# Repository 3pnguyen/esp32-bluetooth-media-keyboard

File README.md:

# esp32-bluetooth-media-keyboard 

## Electronic project that provides the same control as wireless earbuds.

<div align="center">
  
</div>

## ✨ About

This is a repostiory for an electroincs project designed to fit in an Altoids tin with wireless capability to control music playback via Bluetooth. Featuring a 400mAh battery, the circuit also includes a voltage divider + voltage follower setup to reliably measure the battery level & a micro limit switch to trigger sleeping when not in use. The user interface is equiped with 4 push buttons + a compact RGB LED.

When I created the initial prototype (and didn't finish the project), I was not as developed in my electronics skill. Due to being picked up for [Lionstride's Inventeam](https://github.com/3pnguyen/lionstride-inventeam-2026), the project would go under a 6 month hiatus. Drawing closer to the end of the school year, I realized that I could revive the project better than ever. By 6 months, I leveled up my schematic design game, learned to design PCBs, and use programming tools such as PlatformIO. I decided to redesign nearly the entire thing:

<div align="center">
    <table>
        <tr>
            <td> <p> Before: </p> </td>
            <td> <p> After: </p> </td>
        </tr>
        <tr>
            <td>  </td>
            <td>  </td>
        </tr>
    </table>
</div>

V2 was a big leap from the initial prototype. But it never ended up being created because it was too expensive. So I went with a hybrid version, V3:

<div align="center">
  
</div>

V3 took the pros out of the prototype and V2 - it made the perfect balance of cost and complexity.

It was perfect that the project dragged out the way it did, because I ended up making it better than ever. Other than that, this project has become the benchmark for all of the progress I made in my first year of high school. Other than the project's repository, this is a time capsule for how far I've come - and I'll never forget that.

## 📐 CAD

[Amazing CAD here](https://cad.onshape.com/documents/83f792e68010cb24d3ada2b4/w/ca8c8df538ed234a2d133709/e/c846efb1a51148007d1a6c65?renderMode=0&uiState=69af7c17ebe184b914fd710f)

<div align="center">
    <table>
        <tr>
            <td> <p> Prototype: </p> </td>
            <td> <p> V3: </p> </td>
        </tr>
        <tr>
            <td>  </td>
            <td>  </td>
        </tr>
    </table>
</div>

I was too lazy to finish the CAD for V3   <3

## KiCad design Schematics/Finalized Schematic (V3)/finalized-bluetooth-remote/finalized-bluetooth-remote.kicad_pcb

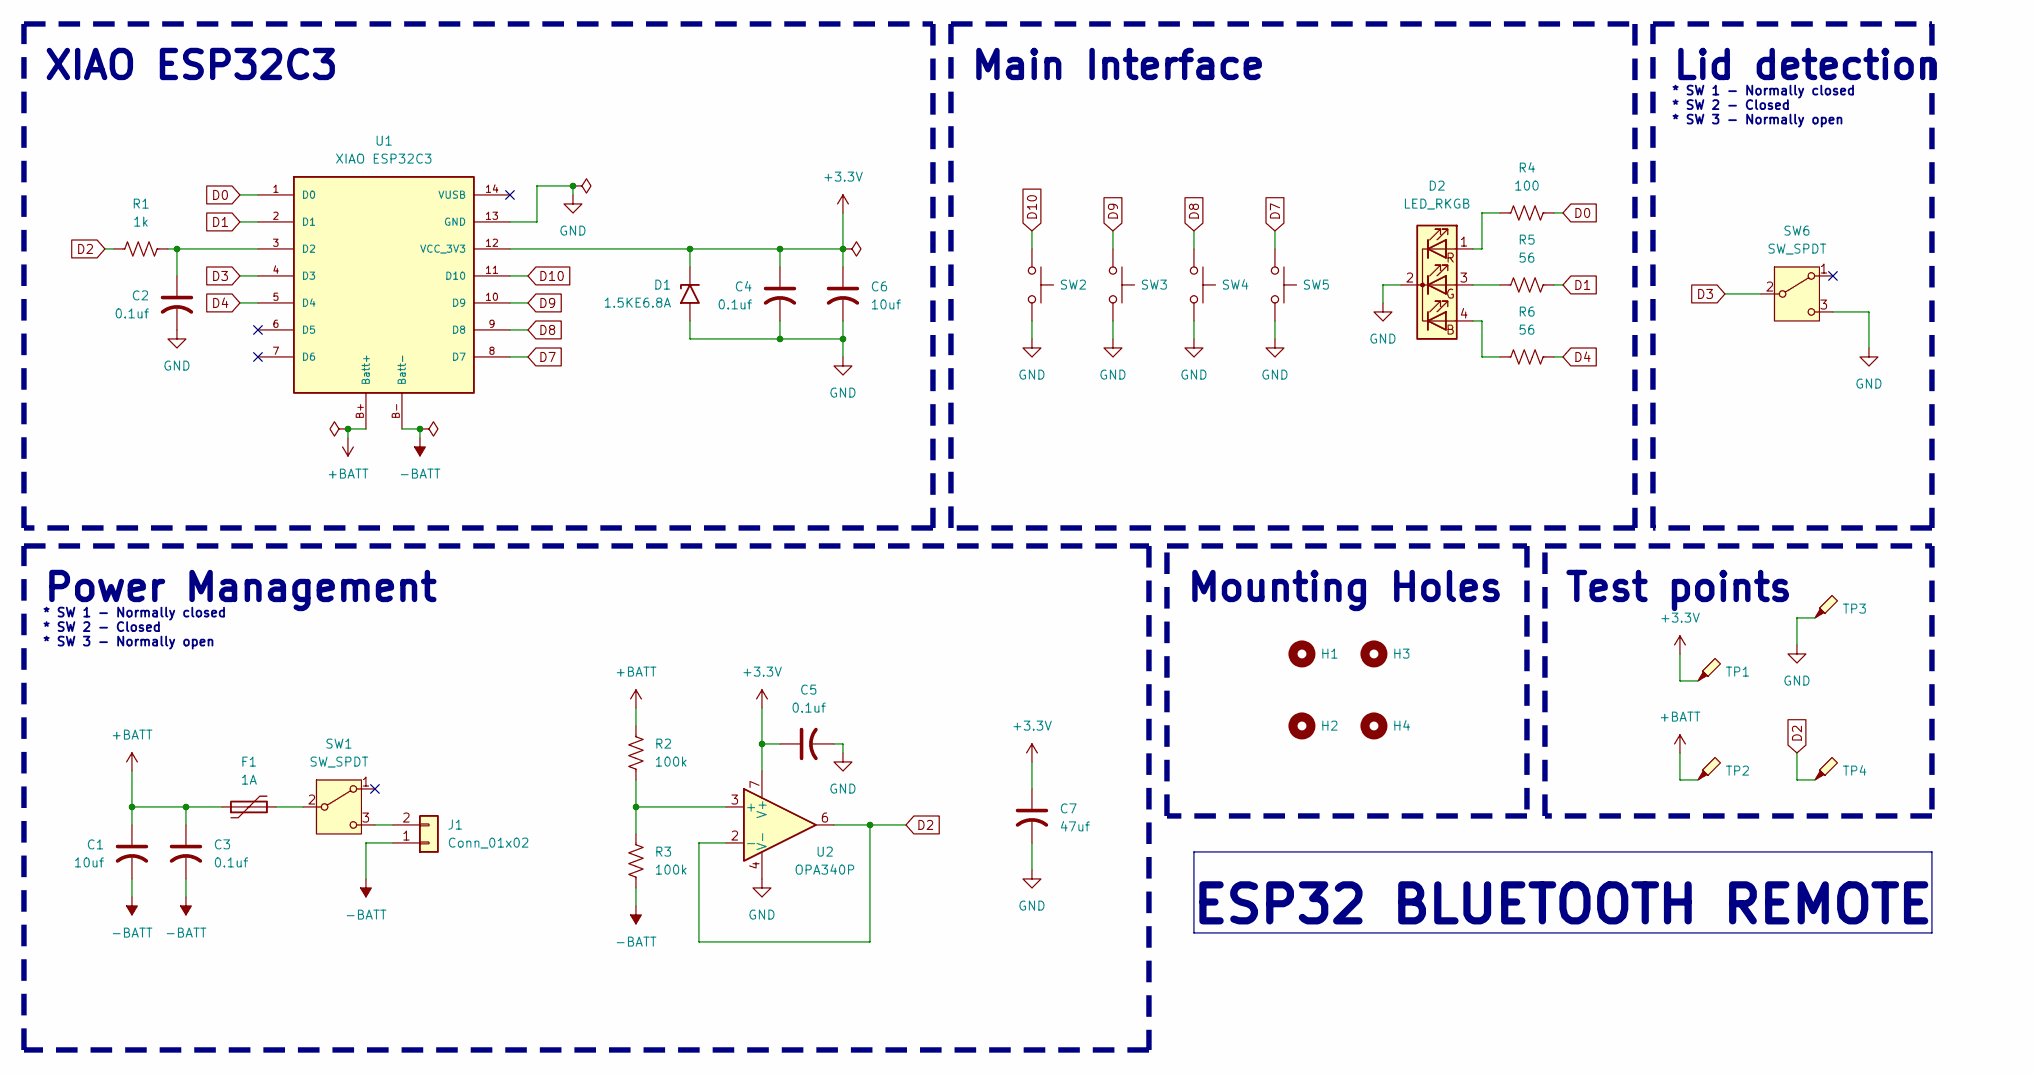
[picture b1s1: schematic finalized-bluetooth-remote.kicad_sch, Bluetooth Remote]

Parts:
C1, C6: 10uf; C_Disc_D5.1mm_W3.2mm_P5.00mm
C2, C3, C4, C5: 0.1uf; C_Disc_D5.1mm_W3.2mm_P5.00mm
C7: 47uf; CP_Radial_D5.0mm_P2.00mm
D1: 1.5KE6.8A; D_DO-201AE_P15.24mm_Horizontal
D2: LED_RKGB; LED_D5.0mm-4_RGB
F1: 1A; Fuse_Bourns_MF-RG300
H1, H2, H3, H4: MountingHole; MountingHole_2.2mm_M2
J1: Conn_01x02; JST_PH_S2B-PH-SM4-TB_1x02-1MP_P2.00mm_Horizontal
R1: 1k; R_Axial_DIN0207_L6.3mm_D2.5mm_P7.62mm_Horizontal
R2, R3: 100k; R_Axial_DIN0207_L6.3mm_D2.5mm_P7.62mm_Horizontal
R4: 100; R_Axial_DIN0207_L6.3mm_D2.5mm_P7.62mm_Horizontal
R5, R6: 56; R_Axial_DIN0207_L6.3mm_D2.5mm_P7.62mm_Horizontal
SW1, SW6: SW_SPDT; PinHeader_1x03_P2.54mm_Vertical
SW2, SW3, SW4, SW5: SW_Push; SW_PUSH_6mm_H7.3mm
TP1, TP2, TP3, TP4: TestPoint_Probe; TestPoint_Pad_D2.0mm
U1: XIAO ESP32C3; Xiao_esp32c3
U2: OPA340P; DIP-8_W7.62mm

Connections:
+3.3V: C4.1, C5.1, C6.1, C7.1, D1.1 (A1), TP1.1, U1.12 (VCC_3V3), U2.7 (V+)
+BATT: C1.1, C3.1, F1.1, R2.1, TP2.1, U1.B+ (Batt+)
-BATT: C1.2, C3.2, J1.1, R3.2, U1.B- (Batt-)
D0: R4.2, U1.1 (D0)
D1: R5.2, U1.2 (D1)
D2: R1.1, TP4.1, U2.2 (-), U2.6
D3: SW6.2 (B), U1.4 (D3)
D4: R6.2, U1.5 (D4)
D7: SW5.1, U1.8 (D7)
D8: SW4.1, U1.9 (D8)
D9: SW3.1, U1.10 (D9)
D10: SW2.1, U1.11 (D10)
GND: C2.2, C4.2, C5.2, C6.2, C7.2, D1.2 (A2), D2.2 (K), SW2.2, SW3.2, SW4.2, SW5.2, SW6.3 (C), TP3.1, U1.13 (GND), U2.4 (V-)
unnamed: D2.4 (BA), R6.1
unnamed: D2.3 (GA), R5.1
unnamed: D2.1 (RA), R4.1
unnamed: J1.2, SW1.3 (C)
unnamed: F1.2, SW1.2 (B)
unnamed: C2.1, R1.2, U1.3 (D2)
unnamed: R2.2, R3.1, U2.3 (+)

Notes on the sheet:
* SW 1 - Normally closed * SW 2 - Closed * SW 3 - Normally open
Mounting Holes
ESP32 BLUETOOTH REMOTE
Lid detection
Main Interface
Power Management
Test points
XIAO ESP32C3

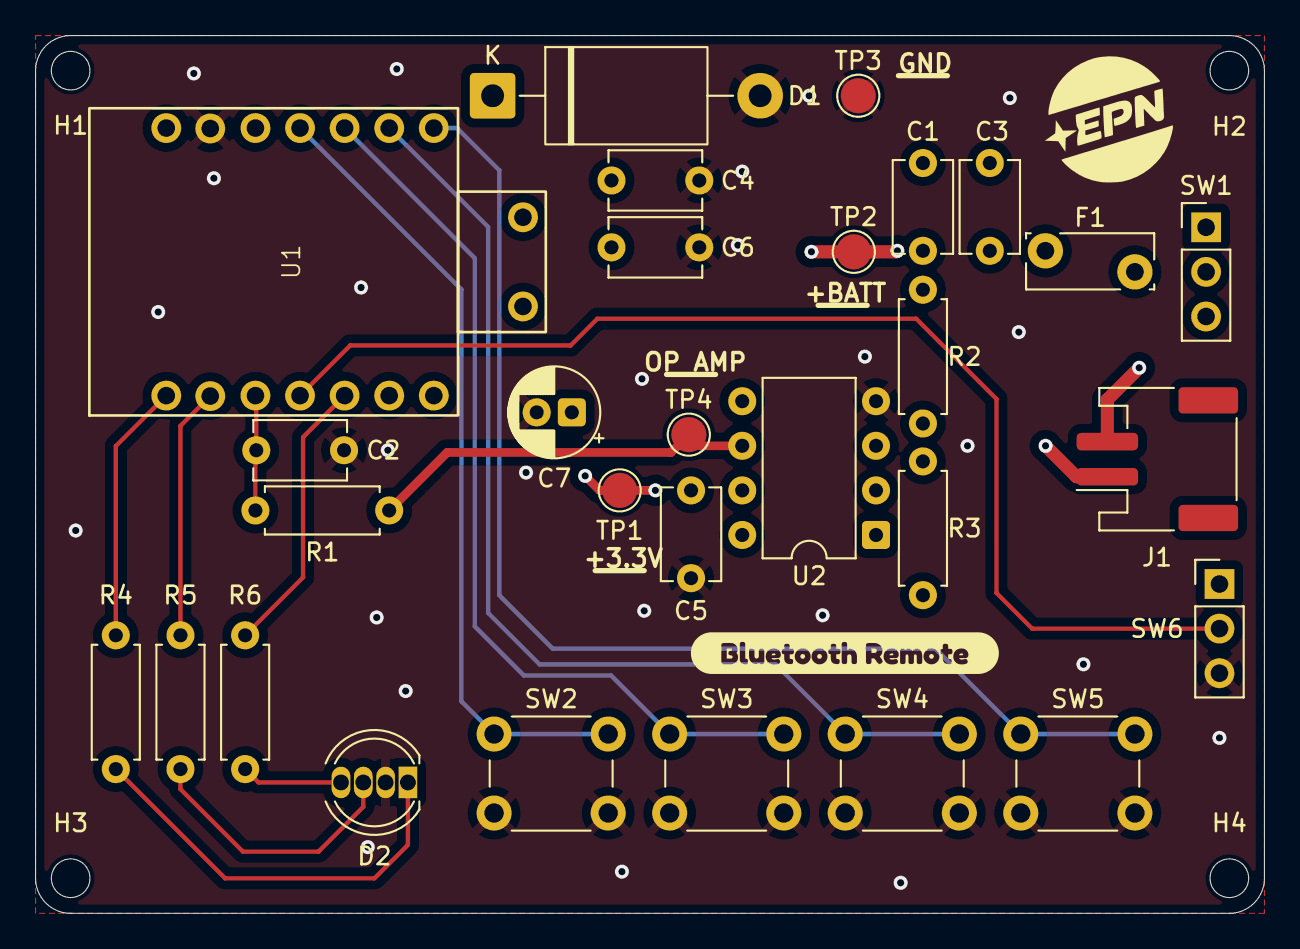
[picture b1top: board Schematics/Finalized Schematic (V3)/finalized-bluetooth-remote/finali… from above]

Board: 4 copper layers, 70.0 x 50.0 mm, 34 parts (0 on the bottom side), 20 nets.

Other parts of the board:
kibuzzard-69E979CA: G***; kibuzzard-69E979CA

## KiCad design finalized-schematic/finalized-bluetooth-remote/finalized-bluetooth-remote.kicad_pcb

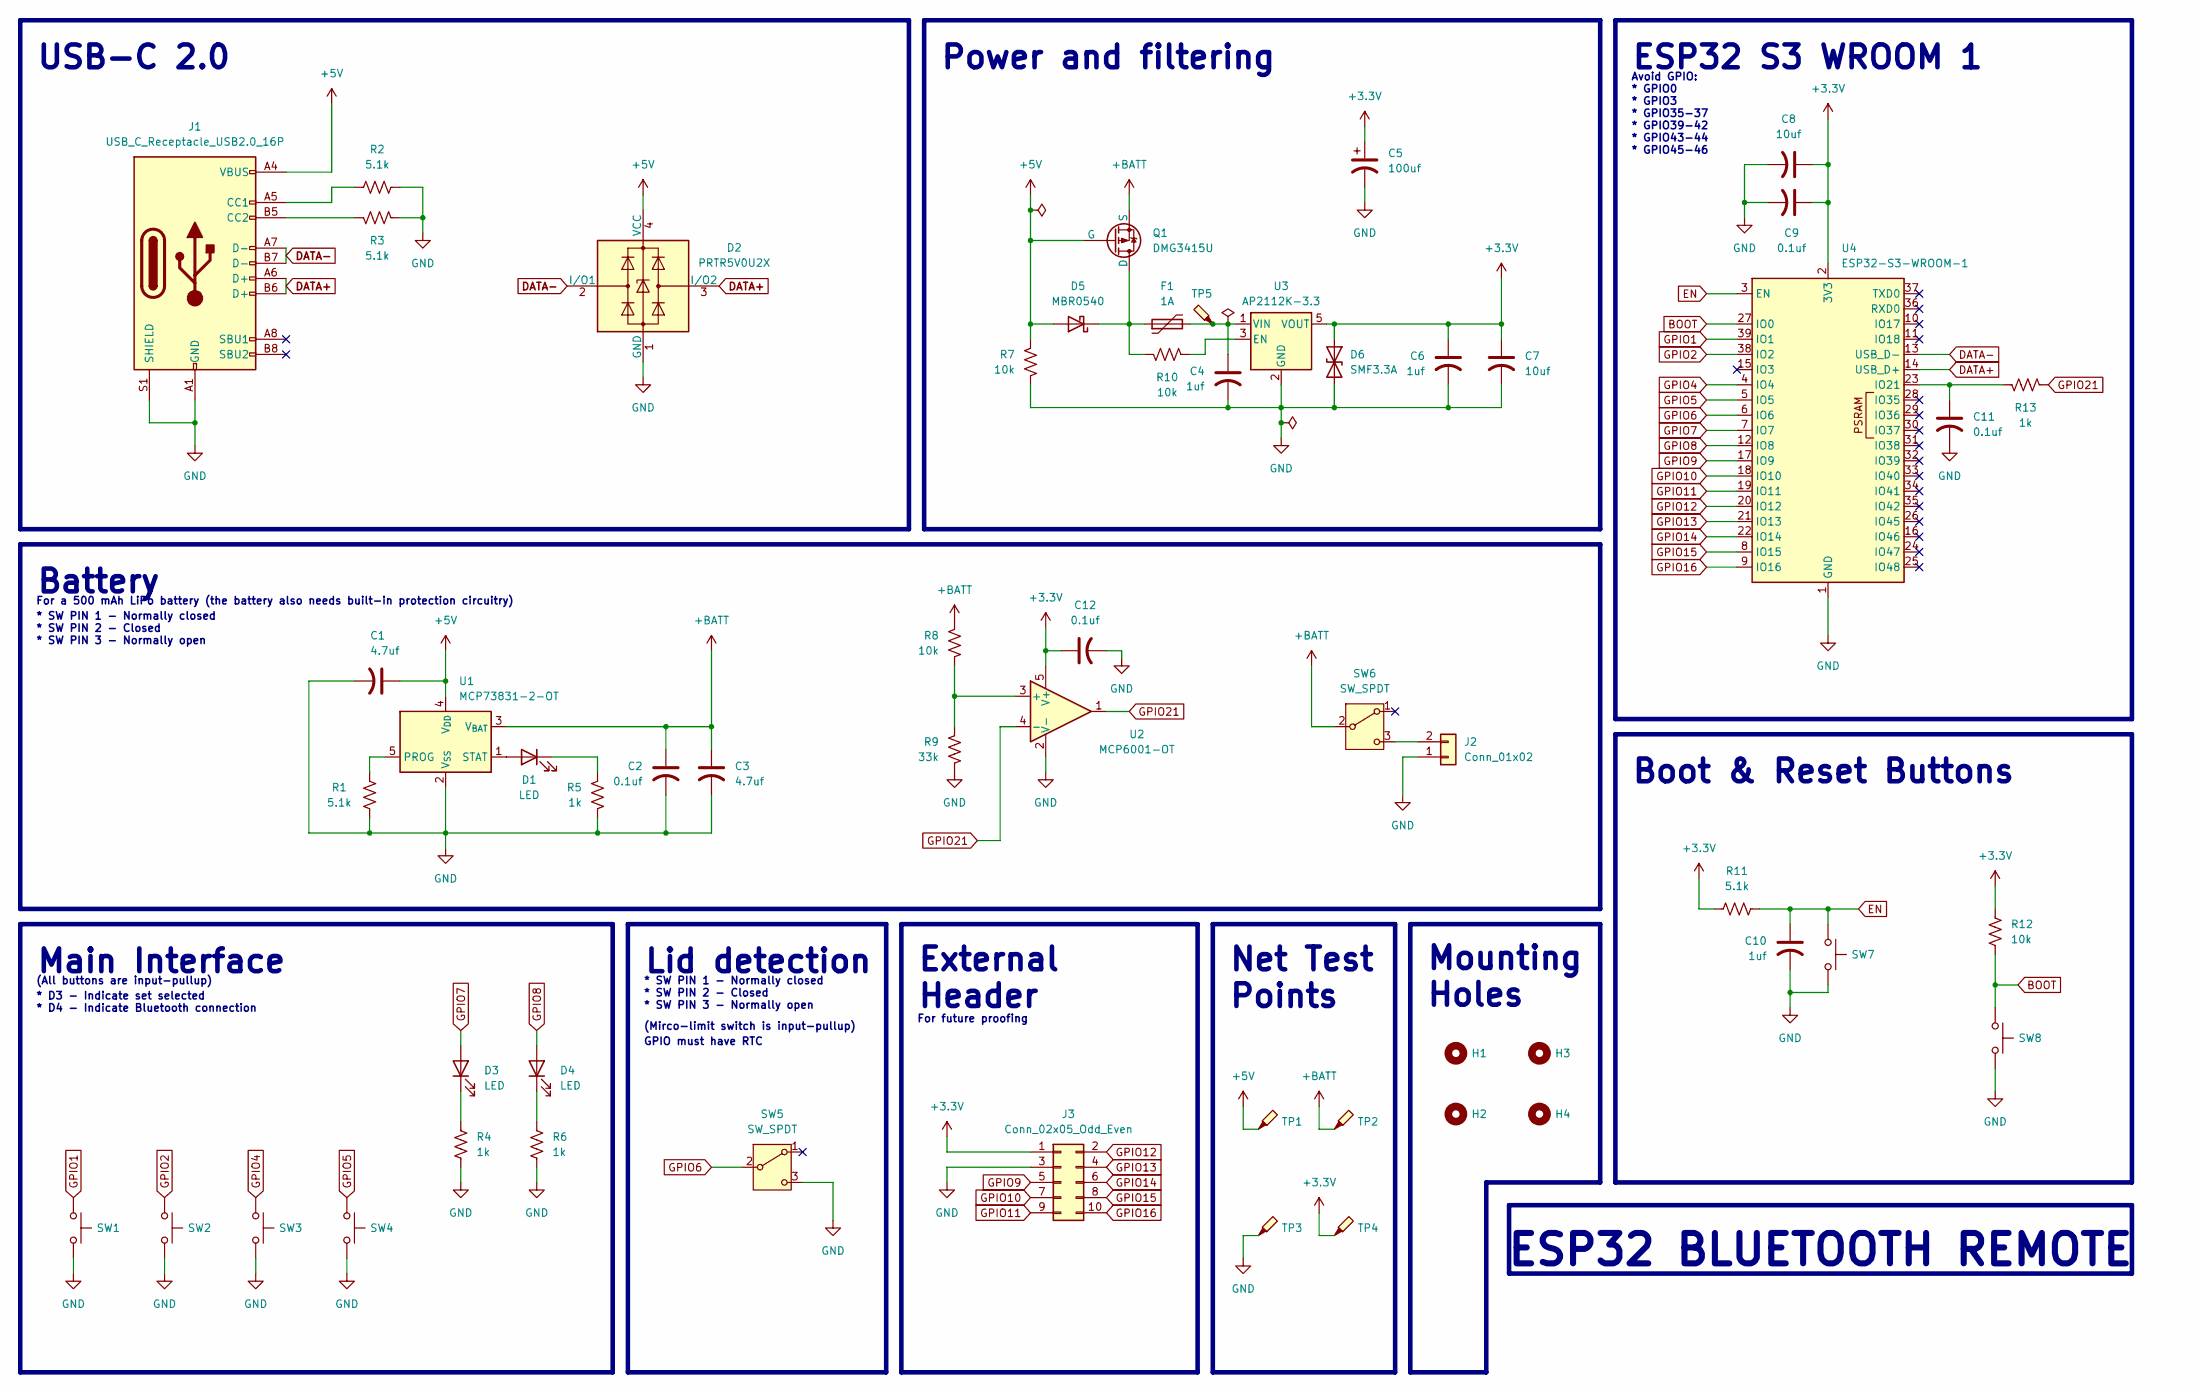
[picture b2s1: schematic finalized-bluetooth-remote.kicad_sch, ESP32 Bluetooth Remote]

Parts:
C1, C3: 4.7uf; C_0805_2012Metric
C2, C9, C11, C12: 0.1uf; C_0603_1608Metric
C4, C6, C10: 1uf; C_0603_1608Metric
C5: 100uf; CP_EIA-7343-31_Kemet-D
C7, C8: 10uf; C_0805_2012Metric
D1, D3, D4: LED; LED_0603_1608Metric
D2: PRTR5V0U2X; SOT-143
D5: MBR0540; D_SOD-123
D6: SMF3.3A; D_SOD-123F
F1: 1A; Fuse_1812_4532Metric
H1, H2, H3, H4: MountingHole; MountingHole_2.2mm_M2
J1: USB_C_Receptacle_USB2.0_16P; USB_C_Receptacle_HRO_TYPE-C-31-M-12
J2: Conn_01x02; JST_PH_S2B-PH-SM4-TB_1x02-1MP_P2.00mm_Horizontal
J3: Conn_02x05_Odd_Even; PinHeader_2x05_P2.54mm_Vertical
Q1: DMG3415U; SOT-23
R1, R2, R3, R11: 5.1k; R_0603_1608Metric
R4, R5, R6, R13: 1k; R_0603_1608Metric
R7, R8, R10, R12: 10k; R_0603_1608Metric
R9: 33k; R_0603_1608Metric
SW1, SW2, SW3, SW4: SW_Push; SW_SPST_Omron_B3FS-100xP
SW5, SW6: SW_SPDT; PinHeader_1x03_P2.54mm_Vertical
SW7, SW8: SW_Push; SW_Push_1P1T_NO_CK_KMR2
TP1, TP2, TP3, TP4, TP5: TestPoint_Probe; TestPoint_Pad_D2.0mm
U1: MCP73831-2-OT; SOT-23-5
U2: MCP6001-OT; SOT-23-5
U3: AP2112K-3.3; SOT-23-5
U4: ESP32-S3-WROOM-1

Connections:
+3.3V: C5.1, C6.1, C7.1, C8.1, C9.1, C12.1, D6.1 (A1), J3.1, R11.1, R12.1, TP4.1, U2.5 (V+), U3.5 (VOUT), U4.2 (3V3)
+5V: C1.1, D2.4 (VCC), D5.2 (A), J1.A4 (VBUS), J1.A9 (VBUS), J1.B4 (VBUS), J1.B9 (VBUS), Q1.2 (G), R7.2, TP1.1, U1.4 (V_{DD})
+BATT: C2.1, C3.1, Q1.3 (S), R8.1, SW6.2 (B), TP2.1, U1.3 (V_{BAT})
BOOT: R12.2, SW8.1, U4.27 (IO0)
DATA+: D2.3 (I/O2), J1.A6 (D+), J1.B6 (D+), U4.14 (USB_D+)
DATA-: D2.2 (I/O1), J1.A7 (D-), J1.B7 (D-), U4.13 (USB_D-)
EN: C10.1, R11.2, SW7.1, U4.3 (EN)
GND: C1.2, C2.2, C3.2, C4.2, C5.2, C6.2, C7.2, C8.2, C9.2, C10.2, C11.2, C12.2, D2.1 (GND), D6.2 (A2), J1.A1 (GND), J1.A12 (GND), J1.B1 (GND), J1.B12 (GND), J1.S1 (SHIELD), J2.1, J3.3, R1.2, R2.2, R3.2, R4.2, R5.2, R6.2, R7.1, R9.2, SW1.2, SW2.2, SW3.2, SW4.2, SW5.3 (C), SW7.2, SW8.2, TP3.1, U1.2 (V_{SS}), U2.2 (V-), U3.2 (GND), U4.1 (GND), U4.40 (GND), U4.41 (GND)
GPIO1: SW1.1, U4.39 (IO1)
GPIO2: SW2.1, U4.38 (IO2)
GPIO4: SW3.1, U4.4 (IO4)
GPIO5: SW4.1, U4.5 (IO5)
GPIO6: SW5.2 (B), U4.6 (IO6)
GPIO7: D3.2 (A), U4.7 (IO7)
GPIO8: D4.2 (A), U4.12 (IO8)
GPIO9: J3.5, U4.17 (IO9)
GPIO10: J3.7, U4.18 (IO10)
GPIO11: J3.9, U4.19 (IO11)
GPIO12: J3.2, U4.20 (IO12)
GPIO13: J3.4, U4.21 (IO13)
GPIO14: J3.6, U4.22 (IO14)
GPIO15: J3.8, U4.8 (IO15)
GPIO16: J3.10, U4.9 (IO16)
GPIO21: R13.1, U2.1, U2.4 (-)
unnamed: D1.2 (A), U1.1 (STAT)
unnamed: D1.1 (K), R5.1
unnamed: D3.1 (K), R4.1
unnamed: D4.1 (K), R6.1
unnamed: D5.1 (K), F1.1, Q1.1 (D), R10.1
unnamed: J1.A5 (CC1), R2.1
unnamed: J1.B5 (CC2), R3.1
unnamed: J2.2, SW6.3 (C)
unnamed: R1.1, U1.5 (PROG)
unnamed: R8.2, R9.1, U2.3 (+)
unnamed: R10.2, U3.3 (EN)
unnamed: C4.1, F1.2, TP5.1, U3.1 (VIN)
unnamed: C11.1, R13.2, U4.23 (IO21)

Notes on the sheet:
Net Test Points
For a 500 mAh LiPo battery (the battery also needs built-in protection circuitry)
GPIO must have RTC
ESP32 S3 WROOM 1
Avoid GPIO: * GPIO0 * GPIO3 * GPIO35-37 * GPIO39-42 * GPIO43-44 * GPIO45-46
Main Interface
USB-C 2.0
Power and filtering
Lid detection
Battery
* D3 - Indicate set selected * D4 - Indicate Bluetooth connection
External Header
* SW PIN 1 - Normally closed * SW PIN 2 - Closed * SW PIN 3 - Normally open
Boot & Reset Buttons
ESP32 BLUETOOTH REMOTE
Mounting Holes
For future proofing
(Mirco-limit switch is input-pullup)
(All buttons are input-pullup)

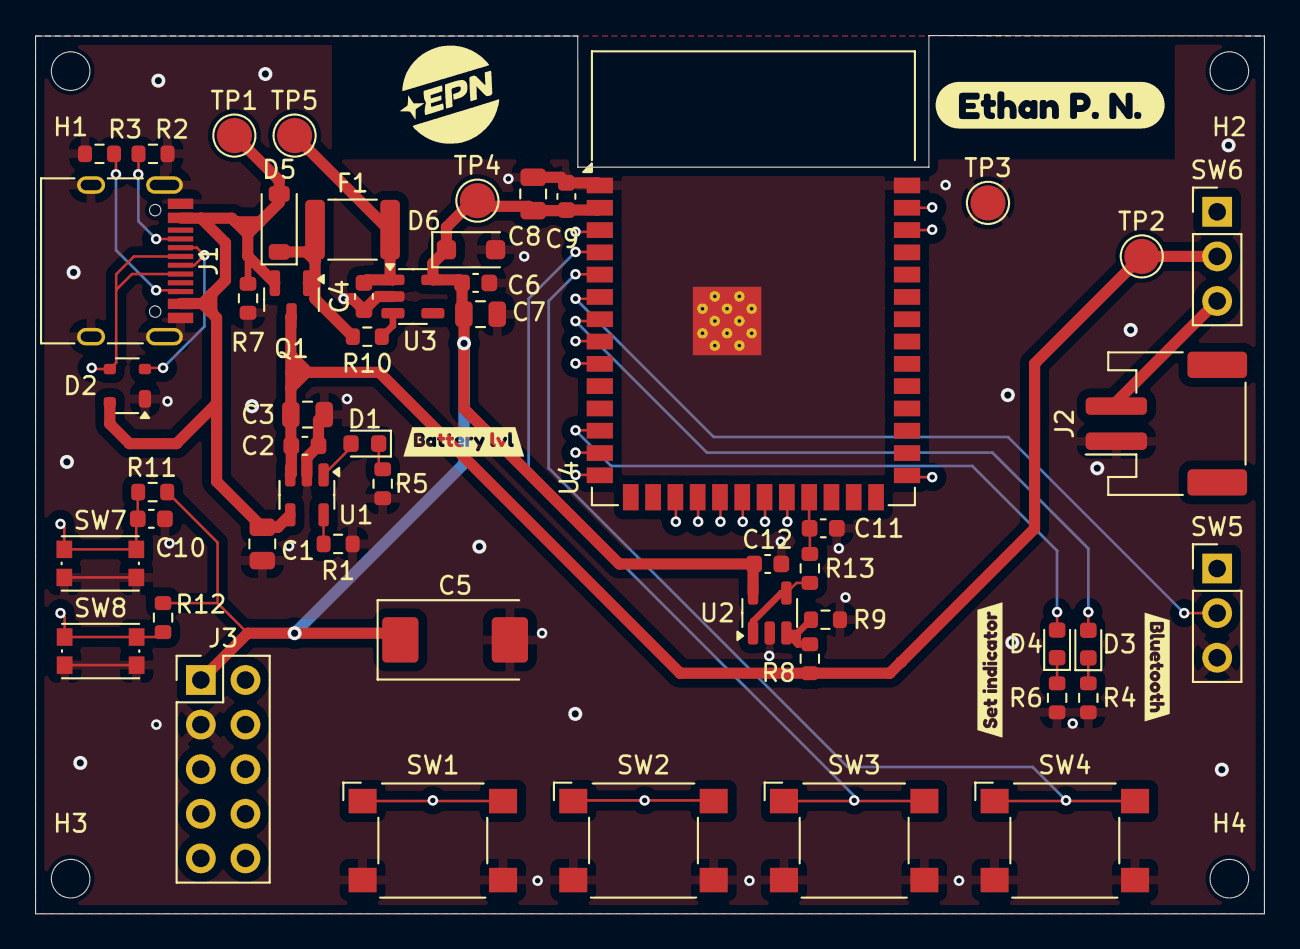
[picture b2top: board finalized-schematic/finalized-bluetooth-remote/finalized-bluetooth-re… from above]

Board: 4 copper layers, 70.0 x 50.0 mm, 61 parts (0 on the bottom side), 37 nets.

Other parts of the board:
kibuzzard-69D59D66: G***; kibuzzard-69D59D66
kibuzzard-69D59D85: G***; kibuzzard-69D59D85
kibuzzard-69D59DAB: G***; kibuzzard-69D59DAB
kibuzzard-69D59DBA: G***; kibuzzard-69D59DBA

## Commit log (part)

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2025-11-04 Add files via upload
    code added
2025-11-16 Add files via upload
    re-added code but not in a file this time
2025-11-28 Enhance README with project description and schematic
    Added sections for project details and schematic.
2026-04-06 Reformat repo for improvements
2026-04-06 Finished finalized schematic
2026-04-08 finished PCB design
2026-04-08 finished version of finalized schematic
2026-04-09 Schematic version 3
2026-04-10 Assigned footprints for PCB
2026-04-23 Moved files + finished PCB V3
2026-04-23 Confirm PCB V3
2026-04-23 Rename folders and initialize PlatformIO code
2026-04-23 Update README with new images and links
2026-04-23 Fix image source in README for finalized schematic
    Corrected image source path for finalized schematic.
2026-04-23 Transfered old code to PlatformIO
2026-04-23 Clean up classes in code
2026-04-25 removed function header and cpp
2026-04-25 Fixed LEDs blinking during sleep
2026-04-25 Added back func. h + cpp & moved object delcarations
2026-04-25 Removed TimeDebounce class
2026-05-07 Added step file
2026-05-07 Filled in README
2026-05-09 Update resistors for LED
2026-05-09 Update pins for schematic V3
2026-05-09 Update GPIO for V3
2026-05-10 Improved test code
2026-05-11 Update VD in code
2026-05-11 Created constants folder
2026-05-11 Fixed battery readings
2026-05-12 Finished project
2026-05-15 Dimmed the LEDs + fixed bug with the indicator LED
2026-05-16 Fixed bugs from previous commit + dimmed LEDs more
